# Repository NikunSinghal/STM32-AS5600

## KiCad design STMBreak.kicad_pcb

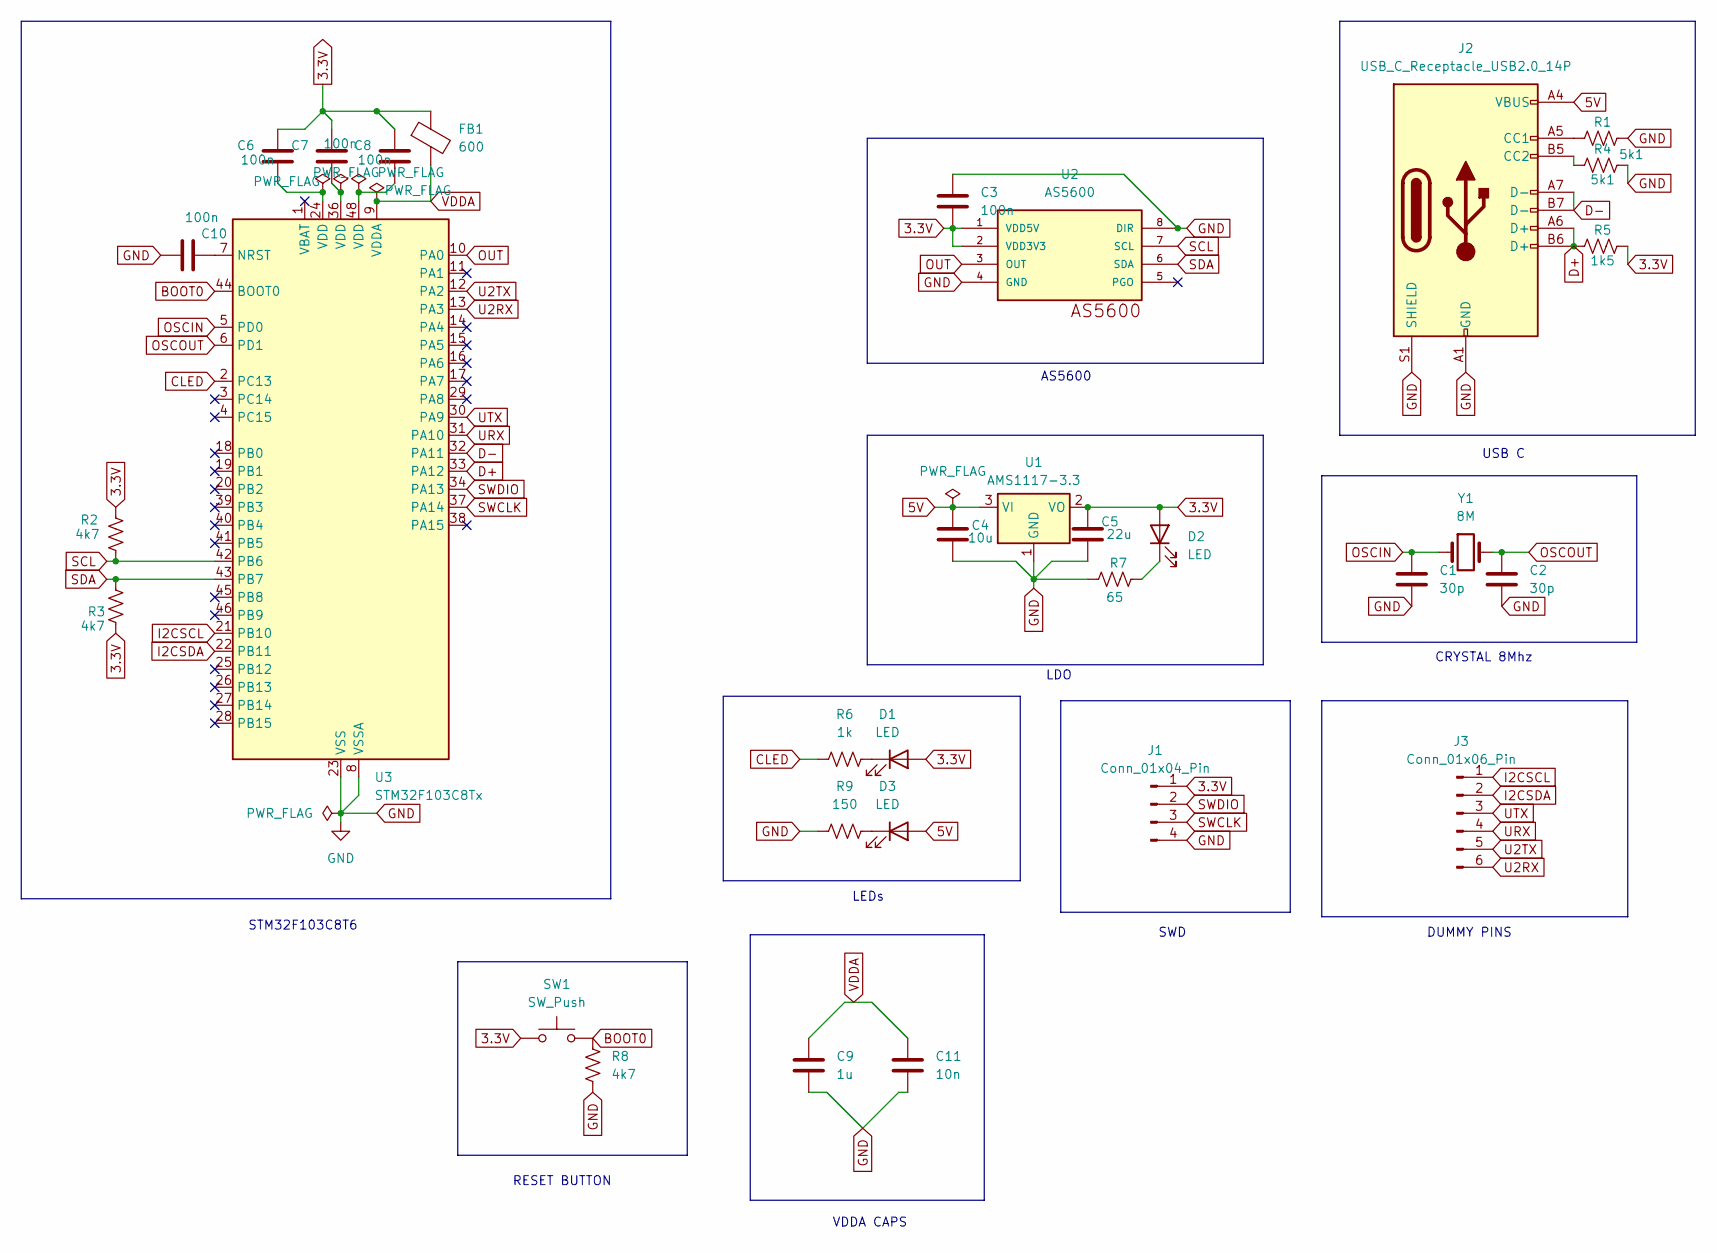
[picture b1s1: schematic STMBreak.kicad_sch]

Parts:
C1: 30p; C_0805_2012Metric_Pad1.18x1.45mm_HandSolder
C2: 30p; C_0603_1608Metric_Pad1.08x0.95mm_HandSolder
C3, C6, C7, C8, C10: 100n; C_0603_1608Metric_Pad1.08x0.95mm_HandSolder
C4: 10u; C_0603_1608Metric_Pad1.08x0.95mm_HandSolder
C5: 22u; C_0603_1608Metric_Pad1.08x0.95mm_HandSolder
C9: 1u; C_0603_1608Metric_Pad1.08x0.95mm_HandSolder
C11: 10n; C_0603_1608Metric_Pad1.08x0.95mm_HandSolder
D1, D2, D3: LED; LED_0603_1608Metric_Pad1.05x0.95mm_HandSolder
FB1: 600; FB_LI0603G121R-10
J1: Conn_01x04_Pin; PinHeader_1x04_P2.54mm_Vertical
J2: USB_C_Receptacle_USB2.0_14P; USB_C_Receptacle_GCT_USB4105-xx-A_16P_TopMnt_Horizontal
J3: Conn_01x06_Pin; PinSocket_1x06_P2.54mm_Vertical
R1, R4: 5k1; R_0603_1608Metric_Pad0.98x0.95mm_HandSolder
R2, R3, R8: 4k7; R_0603_1608Metric_Pad0.98x0.95mm_HandSolder
R5: 1k5; R_0603_1608Metric_Pad0.98x0.95mm_HandSolder
R6: 1k; R_0603_1608Metric_Pad0.98x0.95mm_HandSolder
R7: 65; R_0603_1608Metric_Pad0.98x0.95mm_HandSolder
R9: 150; R_0603_1608Metric_Pad0.98x0.95mm_HandSolder
SW1: SW_Push; SW_TS09-63-25-R-260-SMT-TR
U1: AMS1117-3.3; SOT-223-3_TabPin2
U2: AS5600; SOIC8
U3: STM32F103C8Tx; LQFP-48_7x7mm_P0.5mm
Y1: 8M; Crystal_SMD_Abracon_ABM3-2Pin_5.0x3.2mm_HandSoldering

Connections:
3.3V: C3.2, C5.1, C6.1, C7.1, C8.1, D1.2 (A), D2.2 (A), FB1.1, J1.1, R2.1, R3.2, R5.2, SW1.1, U1.2 (VO), U2.1 (VDD5V), U2.2 (VDD3V3)
5V: C4.1, D3.2 (A), J2.A4 (VBUS), J2.A9 (VBUS), J2.B4 (VBUS), J2.B9 (VBUS), U1.3 (VI)
BOOT0: R8.2, SW1.2, U3.44 (BOOT0)
CLED: R6.1, U3.2 (PC13)
D+: J2.A6 (D+), J2.B6 (D+), R5.1, U3.33 (PA12)
D-: J2.A7 (D-), J2.B7 (D-), U3.32 (PA11)
GND: C1.2, C2.2, C3.1, C4.2, C5.2, C9.2, C10.2, C11.2, J1.4, J2.A1 (GND), J2.A12 (GND), J2.B1 (GND), J2.B12 (GND), J2.S1 (SHIELD), R1.2, R4.2, R7.1, R8.1, R9.1, U1.1 (GND), U2.4 (GND), U2.8 (DIR), U3.8 (VSSA), U3.23 (VSS), U3.35 (VSS), U3.47 (VSS)
I2CSCL: J3.1, U3.21 (PB10)
I2CSDA: J3.2, U3.22 (PB11)
unnamed: C6.2, U3.24 (VDD)
unnamed: C7.2, U3.36 (VDD)
unnamed: C8.2, U3.48 (VDD)
unnamed: D1.1 (K), R6.2
unnamed: D2.1 (K), R7.2
unnamed: D3.1 (K), R9.2
unnamed: J2.A5 (CC1), R1.1
unnamed: J2.B5 (CC2), R4.1
unnamed: C10.1, U3.7 (NRST)
OSCIN: C1.1, U3.5 (PD0), Y1.1
OSCOUT: C2.1, U3.6 (PD1), Y1.2
OUT: U2.3 (OUT), U3.10 (PA0)
SCL: R2.2, U2.7 (SCL), U3.42 (PB6)
SDA: R3.1, U2.6 (SDA), U3.43 (PB7)
SWCLK: J1.3, U3.37 (PA14)
SWDIO: J1.2, U3.34 (PA13)
U2RX: J3.6, U3.13 (PA3)
U2TX: J3.5, U3.12 (PA2)
URX: J3.4, U3.31 (PA10)
UTX: J3.3, U3.30 (PA9)
VDDA: C9.1, C11.1, FB1.2, U3.9 (VDDA)

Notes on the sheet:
VDDA CAPS
STM32F103C8T6
LEDs
DUMMY PINS
CRYSTAL 8Mhz
LDO
AS5600
RESET BUTTON
USB C
SWD

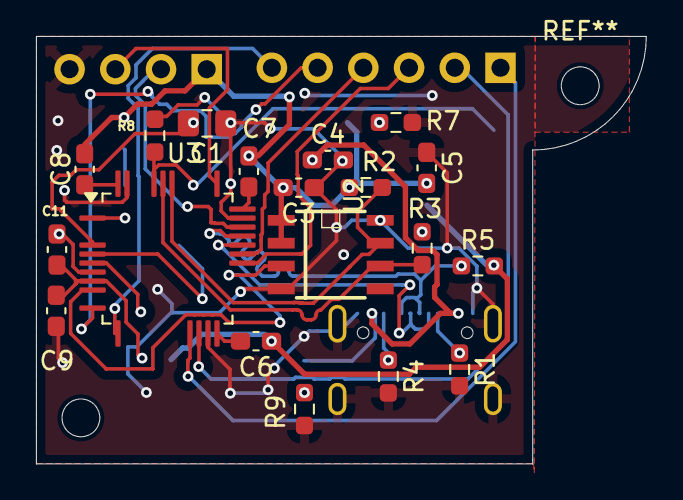
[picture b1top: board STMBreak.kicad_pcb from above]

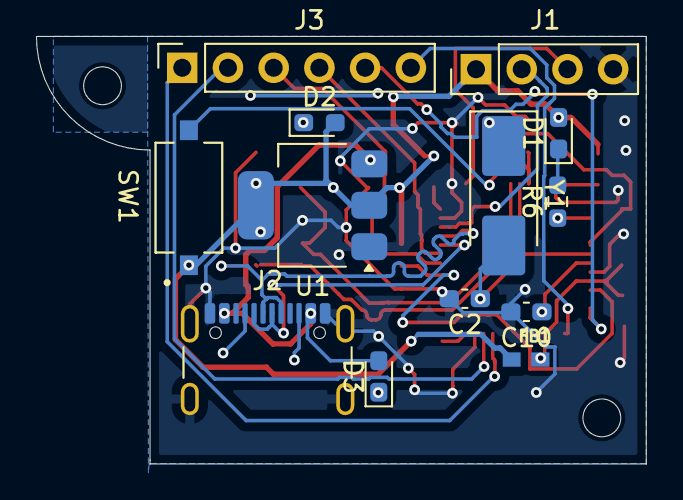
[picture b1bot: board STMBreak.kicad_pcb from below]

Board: 2 copper layers, 33.9 x 23.8 mm, 32 parts (13 on the bottom side), 30 nets.

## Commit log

2026-02-13 Add files via upload
    First Iteration
2026-02-15 Add files via upload
    Capacitors, ferrite beads and other components added. Traces modified. Ground plane added.
2026-02-16 Added D+ and D- traces with tuning.
2026-02-17 Add files via upload
    Centered AS5600.
2026-02-17 Add files via upload
    Modified design approach.
2026-02-17 Add files via upload
    Updated trace design.
2026-02-18 Add files via upload
    Modified PCB design.
2026-02-19 Add files via upload
    Mounting holes added.
2026-02-19 Add files via upload
    BOM file added.
2026-02-19 Add files via upload
    Modified BOM file.
2026-02-19 Add files via upload
    Modified BOM
2026-02-20 Add files via upload
    Check.
